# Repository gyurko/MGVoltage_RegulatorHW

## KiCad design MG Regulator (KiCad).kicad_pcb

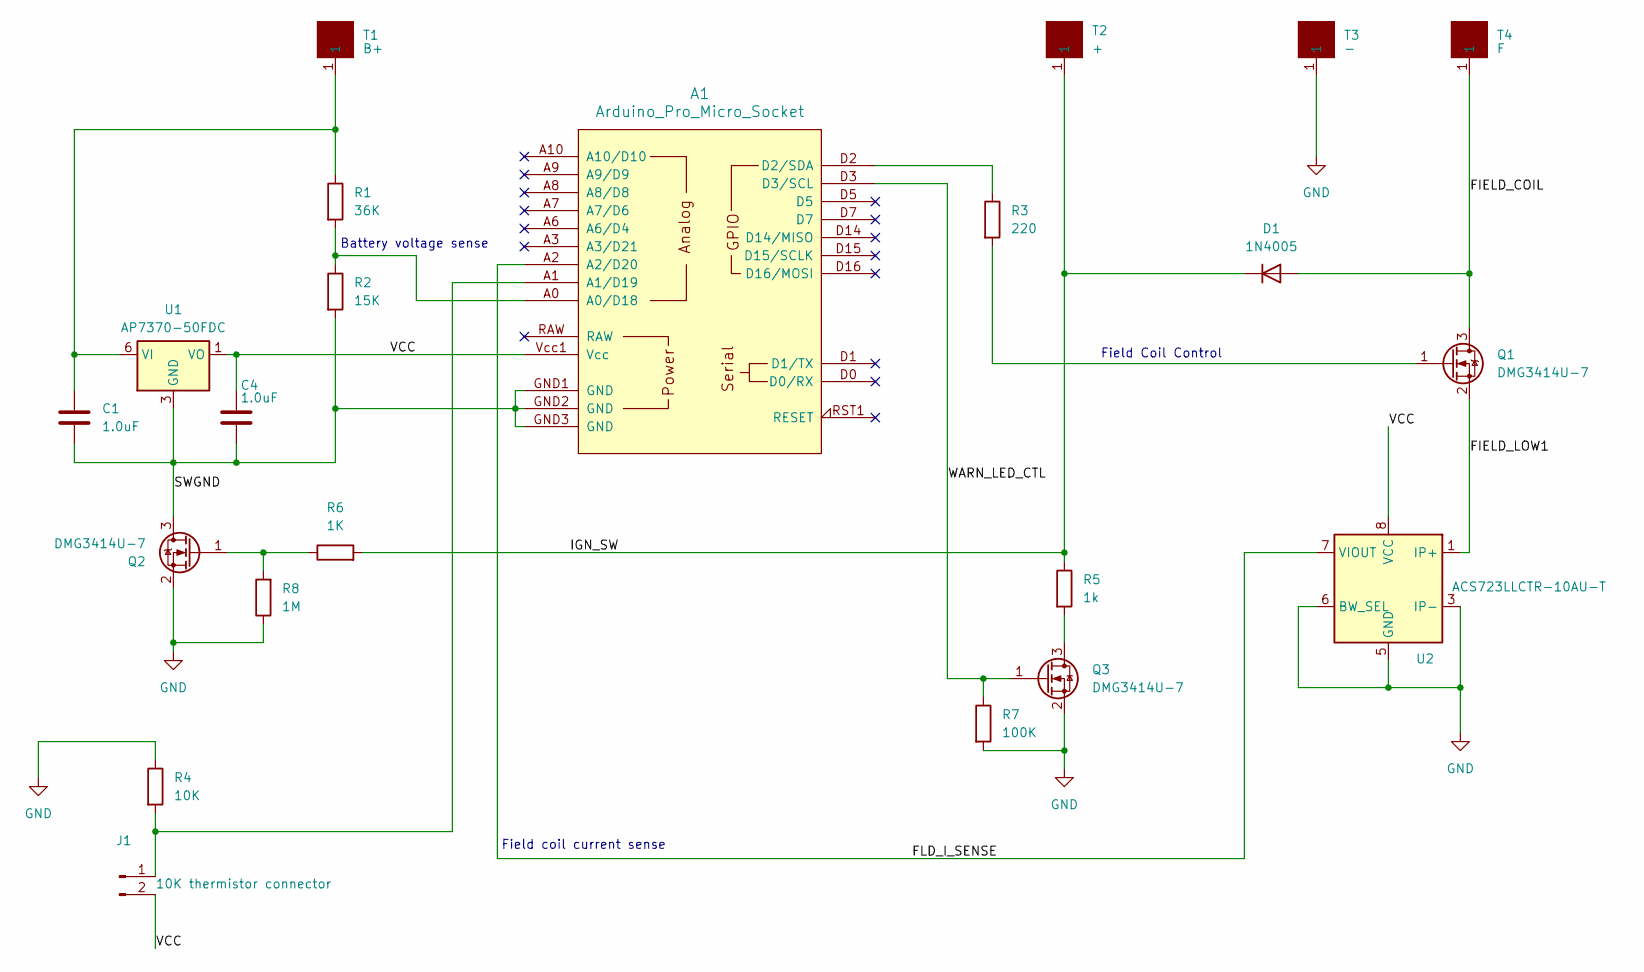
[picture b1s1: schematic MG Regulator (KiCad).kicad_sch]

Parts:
A1: Arduino_Pro_Micro_Socket
C1, C4: 1.0uF; C_0805_2012Metric_Pad1.18x1.45mm_HandSolder
D1: 1N4005; D_DO-41_SOD81_P10.16mm_Horizontal
J1: 10K thermistor connector; PinSocket_1x02_P2.54mm_Vertical
Q1, Q2: DMG3414U-7; TSOT-23
Q3: DMG3414U-7; SOT-23
R1: 36K; R_0805_2012Metric
R2: 15K; R_0805_2012Metric
R3: 220; R_0805_2012Metric
R4: 10K; R_0805_2012Metric
R5: 1k; R_0805_2012Metric
R6: 1K; R_0805_2012Metric
R7: 100K; R_0805_2012Metric
R8: 1M; R_0805_2012Metric
T1: B+; Terminal
T2: +; Terminal
T3: -; Terminal
T4: F; Terminal
U1: AP7370-50FDC; DFN-6-1EP_2x2mm_P0.65mm_EP1.01x1.7mm
U2: ACS723LLCTR-10AU-T; SOIC-8_3.9x4.9mm_P1.27mm

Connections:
/FIELD_COIL: D1.2 (A), Q1.3 (D), T4.1 (1_1)
/FIELD_LOW1: Q1.2 (S), U2.1 (IP+), U2.2 (IP+)
/FLD_I_SENSE: A1.A2 (A2/D20), U2.7 (VIOUT)
/IGN_SW: D1.1 (K), R5.1, R6.2, T2.1 (1_1)
/SWGND: A1.GND1 (GND), A1.GND2 (GND), A1.GND3 (GND), C1.2, C4.2, Q2.3 (D), R2.2, U1.3 (GND), U1.7 (GND); also elsewhere on the board
/VCC: A1.Vcc1 (Vcc), C4.1, J1.2, U1.1 (VO), U2.8 (VCC); also elsewhere on the board
/WARN_LED_CTL: A1.D3 (D3/SCL), Q3.1 (G), R7.1
GND: Q2.2 (S), Q3.2 (S), R4.1, R7.2, R8.1, T3.1 (1_1), U2.3 (IP-), U2.4 (IP-), U2.5 (GND), U2.6 (BW_SEL)
unnamed: A1.A0 (A0/D18), R1.2, R2.1
unnamed: A1.A1 (A1/D19), J1.1, R4.2
unnamed: A1.D2 (D2/SDA), R3.1
unnamed: Q1.1 (G), R3.2
unnamed: Q2.1 (G), R6.1, R8.2
unnamed: Q3.3 (D), R5.2
unnamed: C1.1, R1.1, T1.1 (1_1), U1.6 (VI)

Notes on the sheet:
Battery voltage sense
Field Coil Control
Field coil current sense

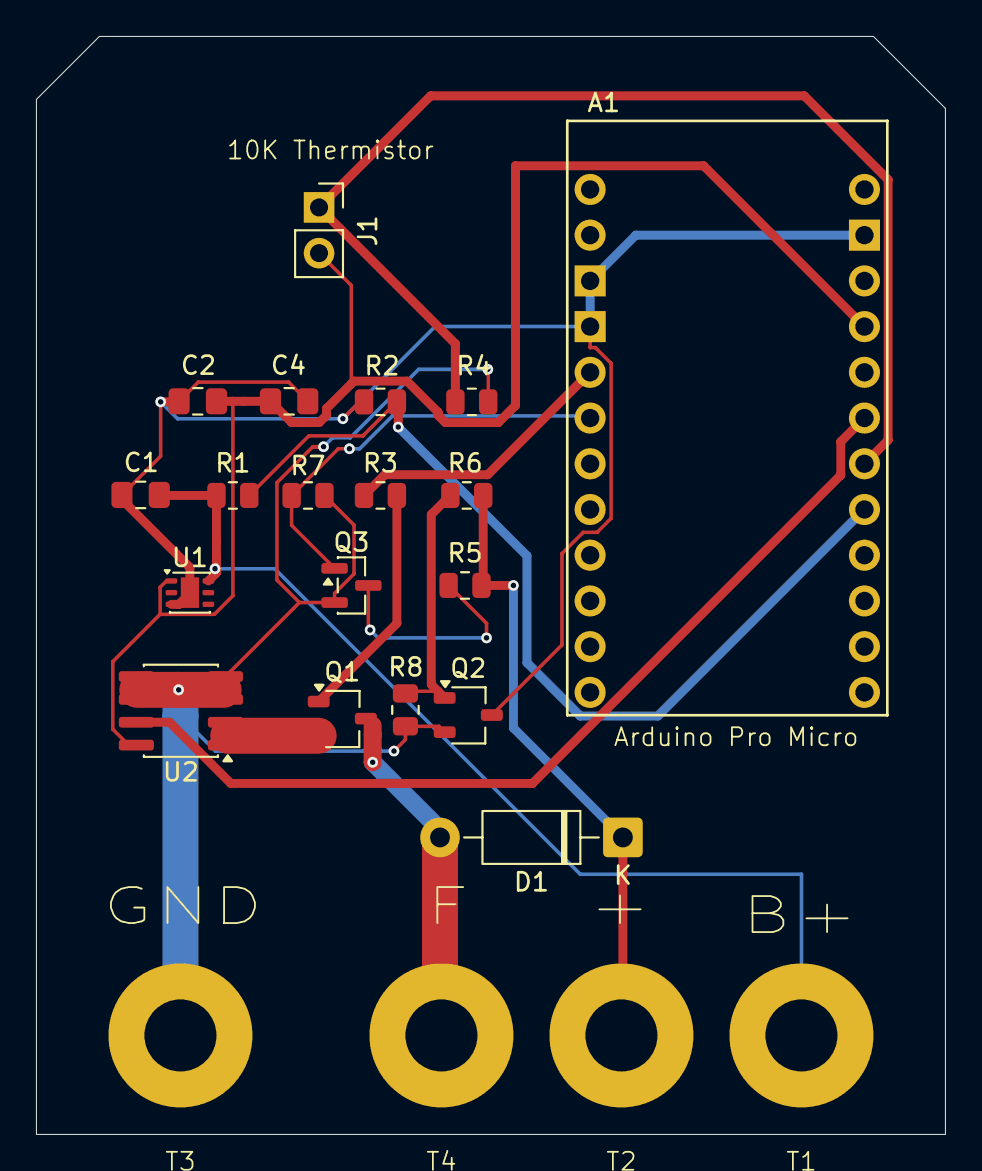
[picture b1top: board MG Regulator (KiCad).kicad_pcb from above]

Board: 2 copper layers, 50.5 x 61.0 mm, 23 parts (0 on the bottom side), 15 nets.

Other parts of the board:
C2: C; C_0805_2012Metric_Pad1.18x1.45mm_HandSolder

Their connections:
/SWGND: C2.2; also elsewhere on the board
/VCC: C2.1; also elsewhere on the board

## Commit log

2026-04-26 Lastest vesion with switch to turn on LED when ignition turns on.
2026-04-26 Small correction to a text field on schematic.
2026-04-26 Modified to be able to control the ignition led and enable arduino power from the ignition switch.
2026-04-26 Minor trace width changes before ordering at JLCPCB.
2026-04-28 Changed the fets to be the same. Fixed the problem with the thermistor not being powered. (this fix isn't on the boards ordered)
